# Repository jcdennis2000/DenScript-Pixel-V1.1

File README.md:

# DenScript-Pixel-V1.1

The DenScript Pixel uses the commonly available WS2812B Addressable RGB LED, which can produce over 16,000,000 colours! Perfect for when you want more LEDs than your Microcontroller can handle.

Rather than taking a current to control the Red, Green and Blue electrodes of a standard RGB LED, the DenScript Pixel only requires a VCC (5V), GND and Data signal. Even better, you can theoretically chain an unlimited number of these together to make exciting LED Displays!!

To make connecting to the module easier, we have colour coded the pins, simply match the colours when connecting multiple Pixels together! The arrow at the base shows the direction of data travel.

Initial Release Date: 28/03/2019

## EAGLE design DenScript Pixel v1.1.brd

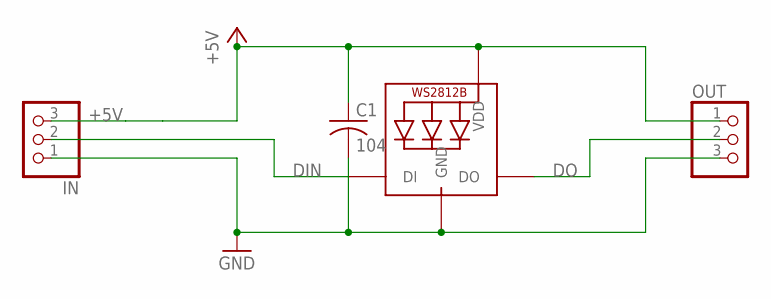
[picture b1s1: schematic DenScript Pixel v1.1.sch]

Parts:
C1: 104; C0603K
IN: PINHD-1X3; 1X03
LED1: WS2812B_5050N; WS2812B-NARROW
OUT: PINHD-1X3; 1X03

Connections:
+5V: C1.1, IN.3, LED1.1-VDD (VDD), OUT.1
DIN: IN.2, LED1.4-DIN (DI)
DO: LED1.2-DOUT (DO), OUT.2
GND: C1.2, IN.1, LED1.3-GND (GND), OUT.3

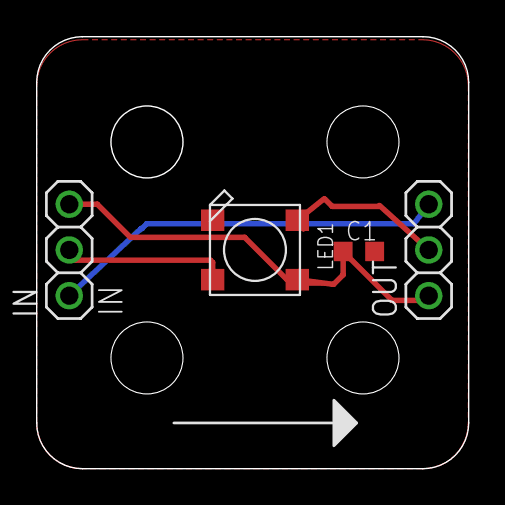
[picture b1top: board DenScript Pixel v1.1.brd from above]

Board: 2 copper layers, 24.0 x 24.0 mm, 4 parts (0 on the bottom side), 4 nets.

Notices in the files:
DenScript Pixel v1.1.brd:
Dennistries Ltd (c) 2019
